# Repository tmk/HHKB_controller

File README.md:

Keyboard Controller Board for HHKB
==================================
This controller makes your HHKB fully programmable. You can use this with [tmk_keyboard] firmware. This will fit HHKB Pro2, Type-S and JP.

[tmk_keyboard]: https://github.com/tmk/tmk_keyboard

You can buy assembled board here. https://geekhack.org/index.php?topic=71517.0

dimension
----
141.50x36.00mm(1.6mm thick)

Update
------
- 2017/06/27: Rev.N     Fix footprint of USB: add SMD pads for frame
- 2017/05/03: Rev.M     Fix footprints of USB, LED, SKHH and DF14
- 2016/08/27: Rev.L     Enlarge TH land of USB connector
- 2016/07/03: Rev.K     Add reverse polarity protection and change foot print of D1
- 2016/01/28: Rev.J     Add TMK logo and remove C13
- 2015/12/01: Rev.I     Changed USB miniB to UX60SC-MB-5S8(through hole)
- 2015/12/01: Rev.H'    Changed lands of USB miniB to recomended size
- 2015/07/xx: Rev.H
- 2015/03/xx: Rev.G
- 2014/12/xx: Rev.F
- 2014/11/xx: Rev.E
- 2014/09/19: Rev.D
- 2014/07/28: Rev.C

LICENSE
-------
TBD

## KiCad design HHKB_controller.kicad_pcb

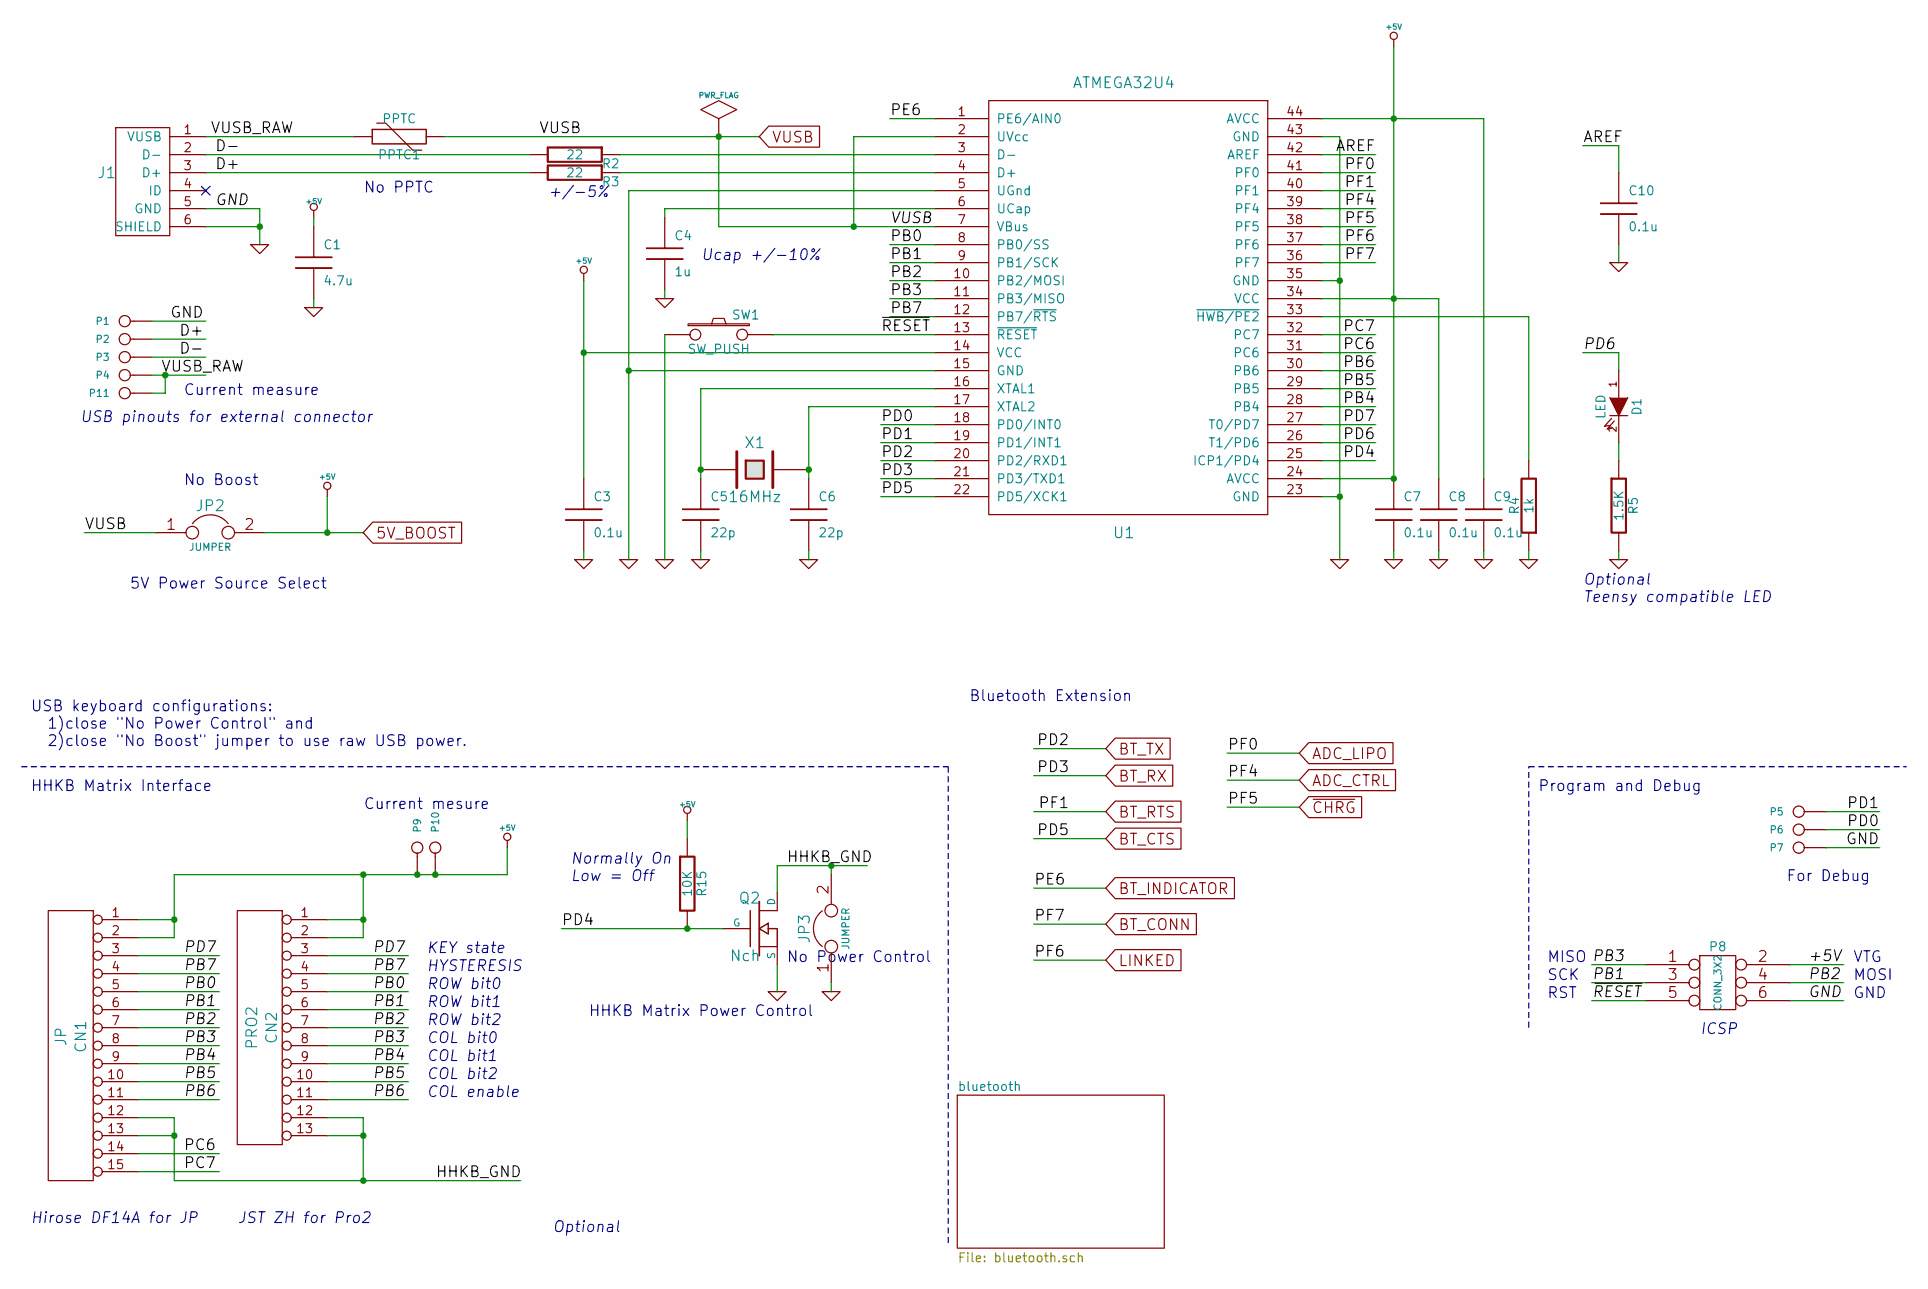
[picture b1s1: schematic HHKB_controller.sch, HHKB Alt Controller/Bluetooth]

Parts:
C1: 4.7u; C_3216
C3, C7, C8, C9, C10: 0.1u; C_1608
C4: 1u; C_1608
C5, C6: 22p; C_1608
CN1: JP; HHKB_JP_HRS_DF14_15P
CN2: PRO2; HHKB_PRO2_ZH13
D1: LED; LED_3020_REFLOW
J1: USB_mini_micro_B; USB_miniB_hirose_new
JP2, JP3: JUMPER; SOLDER_JUMPER_2
P1, P7: GND; PIN_1
P2: D+; PIN_1
P3: D-; PIN_1
P4: VUSB; PIN_1_SQUARE
P5: PD1; PIN_1
P6: PD0; PIN_1
P8: CONN_3X2; AVR_ICSP_3x2
P9, P10, P11: CONN_1; PIN_1
PPTC1: PPTC; PPTC_nano
Q2: Nch; MOS_FET_SOT23-3_HSOL
R2, R3: 22; R_1608
R4: 1k; R_1608
R5: 1.5K; R_1608
R15: 10K; R_1608
SW1: SW_PUSH; SW_TACT_TH_HORIZ_LOW
U1: ATMEGA32U4; QFP44
X1: 16MHz; HC-49_SMT

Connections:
5V_BOOST: C1.1, C3.1, C7.1, C8.1, C9.1, CN1.1, CN1.2, CN2.1, CN2.2, JP2.2, P8.2, P9.1, P10.1, R15.1, U1.14 (VCC), U1.24 (AVCC), U1.34 (VCC), U1.44 (AVCC); also elsewhere on the board
/AREF: C10.1, U1.42 (AREF)
/D+: J1.3 (D+), P2.1, R3.2
/D-: J1.2 (D-), P3.1, R2.2
/HHKB_GND: CN1.12, CN1.13, CN2.12, CN2.13, JP3.2, Q2.D
/PB0: CN1.5, CN2.5, U1.8 (PB0/SS)
/PB1: CN1.6, CN2.6, P8.3, U1.9 (PB1/SCK)
/PB2: CN1.7, CN2.7, P8.4, U1.10 (PB2/MOSI)
/PB3: CN1.8, CN2.8, P8.1, U1.11 (PB3/MISO)
/PB4: CN1.9, CN2.9, U1.28 (PB4)
/PB5: CN1.10, CN2.10, U1.29 (PB5)
/PB6: CN1.11, CN2.11, U1.30 (PB6)
/PB7: CN1.4, CN2.4, U1.12 (PB7/~RTS)
/PC6: CN1.14, U1.31 (PC6)
/PC7: CN1.15, U1.32 (PC7)
/PD0: P6.1, U1.18 (PD0/INT0)
/PD1: P5.1, U1.19 (PD1/INT1)
/PD4: Q2.G, R15.2, U1.25 (ICP1/PD4)
/PD6: D1.1 (A), U1.26 (T1/PD6)
/PD7: CN1.3, CN2.3, U1.27 (T0/PD7)
/VUSB_RAW: J1.1 (VUSB), P4.1, P11.1, PPTC1.1
/~RESET: P8.5, SW1.2, U1.13 (~RESET)
ADC_CTRL: U1.39 (PF4); also elsewhere on the board
ADC_LIPO: U1.41 (PF0); also elsewhere on the board
BT_CONN: U1.36 (PF7); also elsewhere on the board
BT_CTS: U1.22 (PD5/XCK1); also elsewhere on the board
BT_INDICATOR: U1.1 (PE6/AIN0); also elsewhere on the board
BT_RTS: U1.40 (PF1); also elsewhere on the board
BT_RX: U1.21 (PD3/TXD1); also elsewhere on the board
BT_TX: U1.20 (PD2/RXD1); also elsewhere on the board
GND: C1.2, C3.2, C4.2, C5.2, C6.2, C7.2, C8.2, C9.2, C10.2, J1.5 (GND), J1.6 (SHIELD), JP3.1, P1.1, P7.1, P8.6, Q2.S, R4.1, R5.2, SW1.1, U1.5 (UGnd), U1.15 (GND), U1.23 (GND), U1.35 (GND), U1.43 (GND); also elsewhere on the board
LINKED: U1.37 (PF6); also elsewhere on the board
unnamed: C4.1, U1.6 (UCap)
unnamed: C5.1, U1.16 (XTAL1), X1.1
unnamed: C6.1, U1.17 (XTAL2), X1.2
unnamed: D1.2 (K), R5.1
unnamed: R2.1, U1.3 (D-)
unnamed: R3.1, U1.4 (D+)
unnamed: R4.2, U1.33 (~HWB/PE2)
VUSB: JP2.1, PPTC1.2, U1.2 (UVcc), U1.7 (VBus); also elsewhere on the board
~CHRG: U1.38 (PF5); also elsewhere on the board

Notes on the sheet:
USB pinouts for external connector
Ucap +/-10%
+/-5%
Optional Teensy compatible LED
JST ZH for Pro2
KEY state
HYSTERESIS
ROW bit0
ROW bit1
ROW bit2
COL bit0
COL bit1
COL bit2
COL enable
Hirose DF14A for JP
ICSP
VTG
MOSI
MISO
SCK
RST
GND
Bluetooth Extension
For Debug
HHKB Matrix Power Control
Normally On Low = Off
No Power Control
No Boost
USB keyboard configurations: 1)close "No Power Control" and 2)close "No Boost" jumper to use raw USB power.
HHKB Matrix Interface
Program and Debug
Optional
5V Power Source Select
No PPTC
Current mesure
Current measure

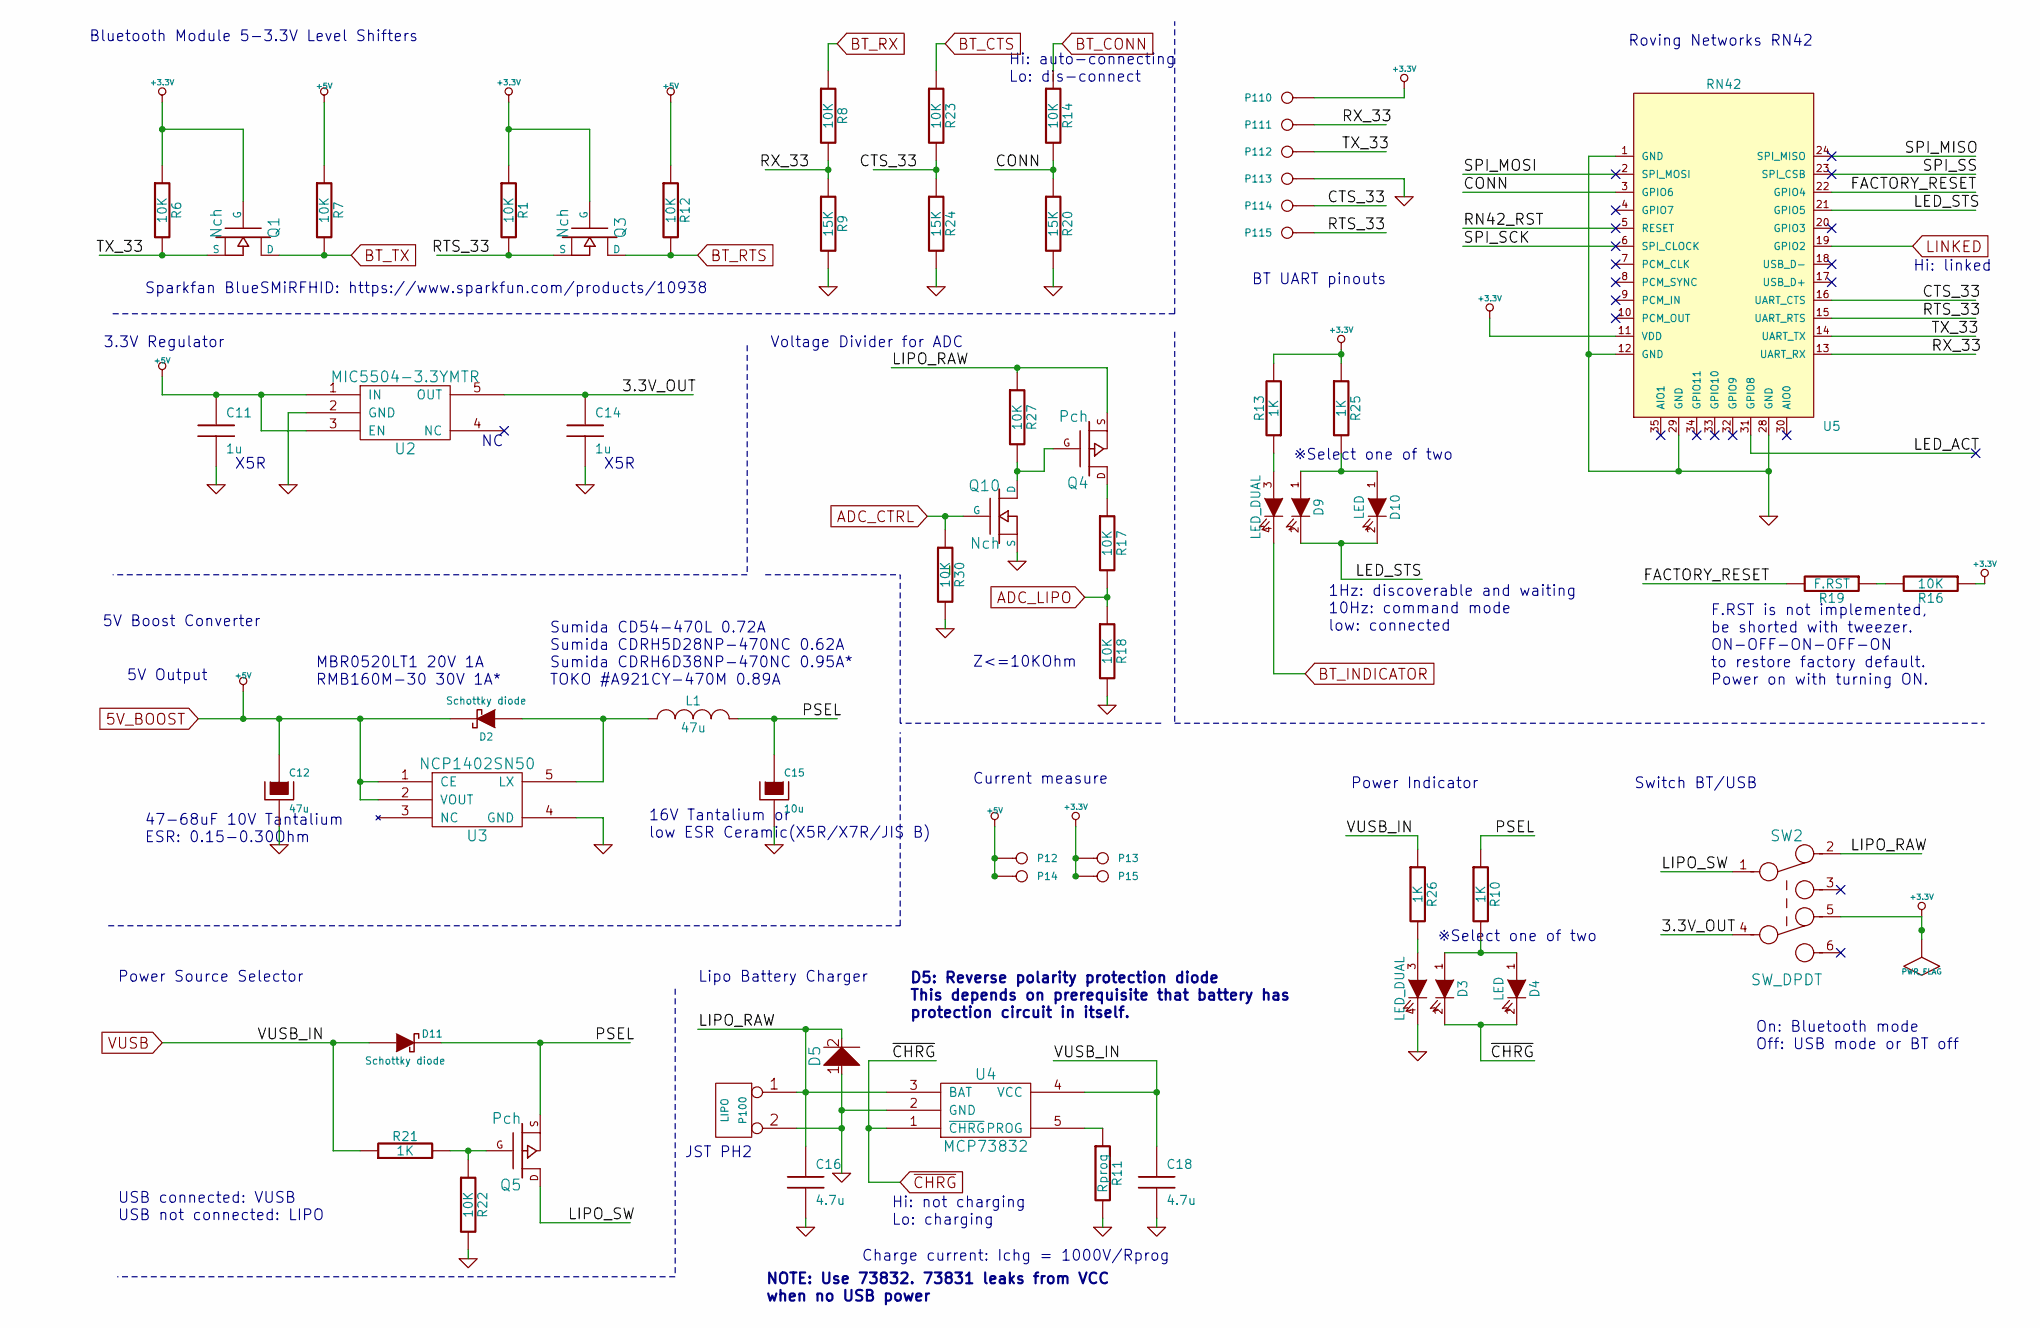
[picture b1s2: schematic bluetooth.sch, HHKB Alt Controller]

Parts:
C11, C14: 1u; C_3216
C12: 47u; C_3528
C15: 10u; C_3528
C16, C18: 4.7u; C_3216
D2, D11: Schottky diode; D_SOD123
D3, D9: LED_DUAL; LED_3025_DUAL
D4, D10: LED; LED_TH
D5: D; D_SOD123
L1: 47u; L_6x6MM
P12, P13, P14, P15, P110, P111, P112, P113, P114, P115: CONN_1; PIN_1
P100: LIPO; JST_PH2_SMT_TH
Q1, Q3, Q10: Nch; MOS_FET_SOT23-3_HSOL
Q4, Q5: Pch; MOS_FET_SOT23-3_HSOL
R1, R6, R7, R8, R12, R14, R16, R17, R18, R22, R23, R27, R30: 10K; R_1608
R9, R20, R24: 15K; R_1608
R10, R13, R21, R25, R26: 1K; R_1608
R11: Rprog; R_1608
R19: F.RST; R_1608_NOGUIDE
SW2: SW_DPDT; SW_MINI_SLIDE
U2: MIC5504-3.3YMTR; SOT23-5_HSOL
U3: NCP1402SN50; SOT23-5_HSOL
U4: MCP73832; SOT23-5_HSOL
U5: RN42

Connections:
5V_BOOST: C11.1, C12.1, D2.2 (K), P12.1, P14.1, R7.1, R12.1, U2.1 (IN), U2.3 (EN), U3.1 (CE), U3.2 (VOUT); also elsewhere on the board
+3.3V: P13.1, P15.1, P110.1, Q1.G, Q3.G, R1.1, R6.1, R13.2, R16.1, R25.1, SW2.5, U5.11 (VDD)
/bluetooth/3.3V_OUT: C14.1, SW2.4, U2.5 (OUT)
/bluetooth/CONN: R14.2, R20.1, U5.3 (GPIO6)
/bluetooth/CTS_33: P114.1, R23.2, R24.1, U5.16 (UART_CTS)
/bluetooth/FACTORY_RESET: R19.2, U5.22 (GPIO4)
/bluetooth/LED_ACT: U5.31 (GPIO8)
/bluetooth/LED_STS: D9.2 (K), D10.2 (K), U5.21 (GPIO5)
/bluetooth/LIPO_RAW: C16.1, D5.2, P100.1, Q4.S, R27.1, SW2.2, U4.3 (BAT)
/bluetooth/LIPO_SW: Q5.D, SW2.1
/bluetooth/PSEL: C15.1, D11.2 (K), L1.2, Q5.S, R10.1
/bluetooth/RN42_RST: U5.5 (RESET)
/bluetooth/RTS_33: P115.1, Q3.S, R1.2, U5.15 (UART_RTS)
/bluetooth/RX_33: P111.1, R8.2, R9.1, U5.13 (UART_RX)
/bluetooth/SPI_MISO: U5.24 (SPI_MISO)
/bluetooth/SPI_MOSI: U5.2 (SPI_MOSI)
/bluetooth/SPI_SCK: U5.6 (SPI_CLOCK)
/bluetooth/SPI_SS: U5.23 (SPI_CSB)
/bluetooth/TX_33: P112.1, Q1.S, R6.2, U5.14 (UART_TX)
ADC_CTRL: Q10.G, R30.1; also elsewhere on the board
ADC_LIPO: R17.2, R18.1; also elsewhere on the board
BT_CONN: R14.1; also elsewhere on the board
BT_CTS: R23.1; also elsewhere on the board
BT_INDICATOR: D9.4 (K); also elsewhere on the board
BT_RTS: Q3.D, R12.2; also elsewhere on the board
BT_RX: R8.1; also elsewhere on the board
BT_TX: Q1.D, R7.2; also elsewhere on the board
GND: C11.2, C12.2, C14.2, C15.2, C16.2, C18.2, D3.4 (K), D5.1, P100.2 (PM), P113.1, Q10.S, R9.2, R11.2, R18.2, R20.2, R22.2, R24.2, R30.2, U2.2 (GND), U3.4 (GND), U4.2 (GND), U5.1 (GND), U5.12 (GND), U5.28 (GND), U5.29 (GND); also elsewhere on the board
LINKED: U5.19 (GPIO2); also elsewhere on the board
unnamed: D2.1 (A), L1.1, U3.5 (LX)
unnamed: D3.1 (A), D4.1 (A), R10.2
unnamed: D3.3 (A), R26.2
unnamed: D9.3 (A), R13.1
unnamed: D9.1 (A), D10.1 (A), R25.2
unnamed: Q4.D, R17.1
unnamed: Q5.G, R21.2, R22.1
unnamed: Q4.G, Q10.D, R27.2
unnamed: R11.1, U4.5 (PROG)
unnamed: R16.2, R19.1
VUSB: C18.1, D11.1 (A), R21.1, R26.1, U4.4 (VCC); also elsewhere on the board
~CHRG: D3.2 (K), D4.2 (K), U4.1 (~CHRG); also elsewhere on the board

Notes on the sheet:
JST PH2
47-68uF 10V Tantalium ESR: 0.15-0.30Ohm
16V Tantalium or low ESR Ceramic(X5R/X7R/JIS B)
5V Boost Converter
3.3V Regulator
Bluetooth Module 5-3.3V Level Shifters
Lipo Battery Charger
Roving Networks RN42
Charge current: Ichg = 1000V/Rprog
5V Output
BT UART pinouts
Voltage Divider for ADC
F.RST is not implemented, be shorted with tweezer. ON-OFF-ON-OFF-ON to restore factory default. Power on with turning ON.
1Hz: discoverable and waiting 10Hz: command mode low: connected
Sparkfan BlueSMiRFHID: https://www.sparkfun.com/products/10938
Power Source Selector
USB connected: VUSB USB not connected: LIPO
※Select one of two
Switch BT/USB
On: Bluetooth mode Off: USB mode or BT off
MBR0520LT1 20V 1A RMB160M-30 30V 1A*
Sumida CD54−470L 0.72A Sumida CDRH5D28NP-470NC 0.62A Sumida CDRH6D38NP-470NC 0.95A* TOKO #A921CY-470M 0.89A
Hi: linked
Hi: auto-connecting Lo: dis-connect
Hi: not charging Lo: charging
Power Indicator
Z<=10KOhm
X5R
NOTE: Use 73832. 73831 leaks from VCC when no USB power
Current measure
D5: Reverse polarity protection diode This depends on prerequisite that battery has protection circuit in itself.

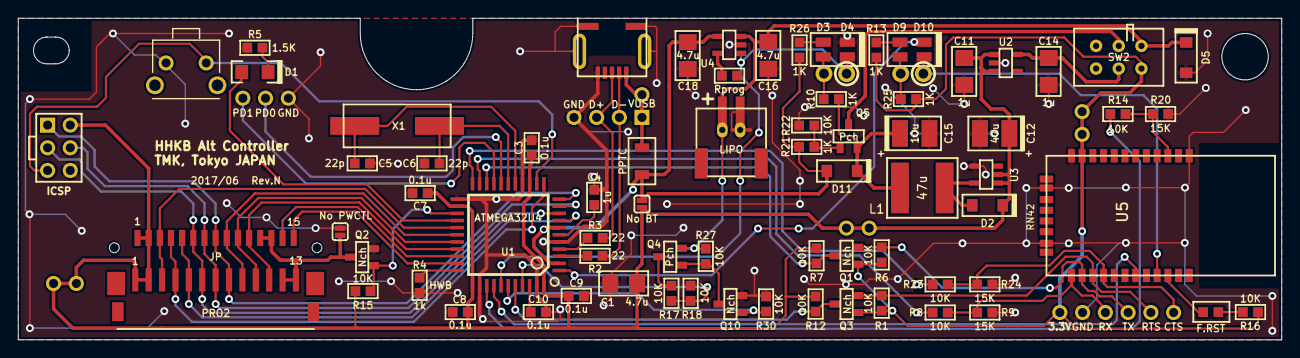
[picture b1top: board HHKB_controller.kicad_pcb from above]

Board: 2 copper layers, 141.5 x 36.0 mm, 94 parts (0 on the bottom side), 63 nets.

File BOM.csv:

Id;Designator;Package;Quantity;Designation;Supplier and ref;
1;R9,R20,R24;keyboard_parts:R_1608;3;15K;1608 5%;
2;R5,R10,R21,R25,R13,R26;keyboard_parts:R_1608;6;1K;1608 5%;
3;R4;keyboard_parts:R_1608;1;1k;1608 5%;
4;R27,R1,R30,R14,R12,R7,R6,R23,R16,R18,R15,R22,R17,R8;keyboard_parts:R_1608;14;10K;1608 5%;
5;R2,R3;keyboard_parts:R_1608;2;22;1608 5%;
6;R11;keyboard_parts:R_1608;1;"Rprog; 2K";1608 5%;
7;CN1;keyboard_parts:HHKB_JP_HRS_DF14_15P;1;JP;Hirose DF14A-15P-1.25H(25);http://www.mouser.jp/ProductDetail/Hirose-Connector/DF14A-15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
8;JP1,JP2,JP3;keyboard_parts:SOLDER_JUMPER_2;3;JUMPER;NONE;
9;C1,C16,C18;keyboard_parts:C_3216;3;4.7u;3216 X7R or X5R;
10;C9,C8,C13,C7,C3,C10;keyboard_parts:C_1608;6;0.1u;1608 any;
11;Q2,Q1,Q10,Q3;keyboard_parts:MOS_FET_SOT23-3_HSOL;4;Nch;ex. BSS138;
12;C14,C11;keyboard_parts:C_3216;2;1u;3216 X7R or X5R;
13;Q5,Q4;keyboard_parts:MOS_FET_SOT23-3_HSOL;2;Pch;ex. IRLML6402;
14;D2,D11,D5;keyboard_parts:D_SOD123;3;Schottky diode;20V 0.5A ex. PMEG2010ER, RB160M-30TR, MBR0520LT1;
15;P6;keyboard_parts:PIN_1;1;PD0;NONE;
16;U4;keyboard_parts:SOT23-5_HSOL;1;MCP73831;Microchip;
17;U3;keyboard_parts:SOT23-5_HSOL;1;NCP1402SN50;ON semi;
18;U2;keyboard_parts:SOT23-5_HSOL;1;MIC5504-3.3YMTR;Micrel;
19;P100;keyboard_parts:JST_PH2_SMT_TH;1;LIPO;3.7V 1000mA;https://www.sparkfun.com/products/339
20;C6,C5;keyboard_parts:C_1608;2;22p;1608 any;
21;C4;keyboard_parts:C_1608;1;1u;1608 10%;
22;U1;keyboard_parts:QFP44;1;ATMEGA32U4;Atmel ATmega32U4-AU TQFP44 ;
23;D9,D3;keyboard_parts:LED_3025_DUAL;2;LED_DUAL;3025 or 3225 ex. SEC2764C, LTST-C155GEKT;
24;CN2;keyboard_parts:HHKB_PRO2_ZH13;1;PRO2;JST S13B-ZR-SM4A-TF(LF)(SN)(P);http://www.digikey.jp/product-detail/ja/S13B-ZR-SM4A-TF(LF)(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
25;D1;keyboard_parts:LED_2012_HSOL;1;LED;3020 ex. SML-012WT;
26;J1;keyboard_parts:USB_miniB_hirose_new;1;USB_mini_micro_B;Hirose UX60SC-MB-5ST;
27;P5;keyboard_parts:PIN_1;1;PD1;NONE;
28;P7,P1;keyboard_parts:PIN_1;2;GND;NONE;
29;P8;keyboard_parts:AVR_ICSP_3x2;1;CONN_3X2;NONE;
30;P110,P111,P112,P113,P114,P115;keyboard_parts:PIN_1;6;CONN_1;NONE;
31;PPTC1;keyboard_parts:PPTC_nano;1;PPTC;Optional Polyswitch nano;
32;R19;keyboard_parts:R_1608_NOGUIDE;1;F.RST;1608 5% 10K;
33;SW1;keyboard_parts:SW_TACT_TH_HORIZ_LOW;1;SW_PUSH;Alps SKHH;
34;U5;keyboard_parts:RN42;1;RN42;Roving Networks RN42-I/RM615;
35;X1;keyboard_parts:HC-49_SMT;1;16MHz;HC-49 16MHz;
36;P4;keyboard_parts:PIN_1_SQUARE;1;VUSB;NONE;
37;P3;keyboard_parts:PIN_1;1;D-;NONE;
38;P2;keyboard_parts:PIN_1;1;D+;NONE;
39;SLP3-200-100-F,SLP3-200-100-F;keyboard_parts:SLP3-200-100-F;2;Val**;BIVAR SLP3-150-100-F/R light pipe;
40;SW2;keyboard_parts:SW_MINI_SLIDE;1;SW_DPDT;NKK SS22SDH2, SS22SDH4;
41;C12;keyboard_parts:C_3528;1;68u;3528 tantalum;
42;C15;keyboard_parts:C_3528;1;10u;3528 tantalum;
43;L1;keyboard_parts:L_6x6MM;1;47u;6mm or 7mm 47uH ex. NR6045T470M, CLF6045T-470M-CA;
44;D4,D10;keyboard_parts:LED_TH_BIVAR;2;LED;Through Hole 3mm LED (Not go together with D3 and D9);

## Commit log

2013-06-03 Add initial files
2013-06-04 Coneect all component
2013-06-15 Add Bluetooth module part
2013-06-18 Finish Rev. A
2013-07-11 Add libraries and fix search path
2013-07-11 Create LICENSE
2013-12-04 Fix dimensions of outlines and move USB connector left to 0.1mm
2013-12-06 Add RN42 circuit symbol
2013-12-09 Add RN42 module
2013-12-09 Rename pdf of Rev.A circuit
2013-12-10 Fix module of HHKB pro2 SMT connector
2013-12-10 Add module of HRS DF14 SMT 15P for HHKB JP
2013-12-12 Add HC-49_SMT module
2013-12-12 Add JST_PH2_SMT
2013-12-12 Fix pin name of JST_PH2_TH
2013-12-13 Replace Lipo connector with SMT component
2013-12-18 Fix USB controller part
2014-03-09 Add Power Source Selector
2014-03-09 Add footprint of PPTC and SOD123
2014-03-12 Design initial Rev.B PCB
2014-03-15 Clean files
2014-03-15 Clean files more
2014-04-11 Fix missing symbol in schematic
2014-07-03 Change module for Schottky diode D2
2014-07-04 Fix many fixes of rev.B errata
2014-07-28 Change for rev.C
2014-07-28 Fix position of right top hole 0.2mm to the right
2014-07-29 Change drill size for switch and LEDs and minor silk fix
2014-07-29 rev.C
2014-08-01 Fix revision in schematic for rev.C
2014-09-06 Fix capacitor values for NCP1402
2014-09-06 Change value 10K to Rprog for charger resistor
2014-09-06 Remove C2
2014-09-06 Remove jumpers of 5V, 3.3V and HHKB amp measure
2014-09-07 Change PTC route to use only for BT
2014-09-07 Add submodule library
2014-09-08 Change schematic for dual LEDs
2014-10-23 Final fixes for Rev.D
2014-10-30 Add TODO and fix BOM for Rev.E development
2014-10-30 Add D5 schottky and change C15 size and C14 value
2014-10-31 Fix ADC switch and light pipe hole size
2014-10-31 Fix UVCC
2014-11-03 Final plot of Rev.E to order PCB
2014-11-04 Add rev.D and E schematics
2014-11-04 Add keyboard_parts submodule and BOM.csv
2014-12-08 Fix Q4 P-ch FET of ADC; exchange Drain and Source
2014-12-08 Remove D5
2014-12-08 Change value of C12; 68u to 47u
2014-12-08 Add current measure pins and change pin pad size
2014-12-08 Update BOM
2014-12-08 Add TODO; Errata for Rev.E
2014-12-08 Add Paste layer cut out
2014-12-08 Remove paste cutout from solder jumpers
2014-12-09 Add fix for Rev.E
2015-01-17 Rev.F: Fix solder paste clearance
2015-03-08 Remove solder jumper for Polyfuse
2015-03-12 Rev.G
2015-05-28 Fix sw board connector for Pro
2015-05-29 Rev.Hp for HHKB Pro
2015-07-05 Rev.H
2015-12-01 Change USB miniB footprint
2015-12-01 Change USB miniB 5ST lands to recommended
2015-12-01 Change USB miniB footprint to 5S8
2015-12-02 Change solder mask clearace for PCBWay
2015-12-02 Fix paste layer of USB miniB 5S8
2015-12-14 Update TODO and README
2016-01-27 Remove unused C13 of MIC5504 voltage regulator
2016-01-28 Add TMK logo
2016-07-03 Change foot print of D1 and Add D5
    Change pad size of LED(D1) for proper reflow
    Add D5 schottky diode for reverse polarity protection
2016-08-27 Enlarge TH land of USB connector
2017-03-30 Change LED, USB connector and TACT switch(Rev.M)
2017-05-02 Fix footprints for HRS DF14 and SKHH
2017-06-26 Fix USB footprint: add SMD pads for frame
